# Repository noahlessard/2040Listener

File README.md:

## 2040Listener

This project contains the Raspberry Pi Pico C SDK Project, and Kicad PCB Project, to manufacture an open source MITM style keystroke interceptor. This style of device intercepts a host's computer request to get keystrokes, relays it to a real USB keyboard, and while returning the responses of typed keys, logs it to a LittleFS file stored in flash memory. This memory persists, and can be accessed through a CDC serial port. This port can be toggled on/off for a "stealth" mode.

USB host/device communication is done using the PIO of Raspberry Pi Pico (RP2040). I built the software with the VSCode Pico Project Extension. It uses several other open source libraries, which can be found in the credits section at the bottom of this readme. 

The PCB is designed around the 0805 footprint for easier soldering, and a simple 2 layer board for cheaper manufacturing.

The general idea of the firmware architecture is that core0 of the 2040 acts as a "fake" USB device to the victim computer, sending both HID and CDC data over USB. Core1 acts as a "fake" host stack to a keyboard. Core1 handles getting data from the HID devices, parsing out what the keystroke is and writes to the 2040's LittleFS file before core0 actually transmits. For more details, see my blog post: https://nlessard.online/projects/2040listener/.

**If you decide to build this device yourself, please use it for educational purposes only, and never use it on a computer that you don't control!**

## GPIO 
(This section is useful for testing on a normal Pico board, where access to GP pins is easier.)
|VCC|VBUS|
|-|-|
|D-|GP 1|
|D+|GP 0|
|CNC Toggle|GP 17|
|Ground|GND|

## Credits
Dual host + device listener example from here: https://github.com/brendena/pico_device_and_host, although I used a fork for the Pico VS Code extension: https://github.com/TheLowSpecPC/pico_device_and_host_updated. LittleFS was ported to Pico in this library: https://github.com/tjko/pico-lfs. I used the Raspberry Pi's foundation for a lot of advice during hardware design: https://pip-assets.raspberrypi.com/categories/814-rp2040/documents/RP-008279-DS-1-hardware-design-with-rp2040.pdf

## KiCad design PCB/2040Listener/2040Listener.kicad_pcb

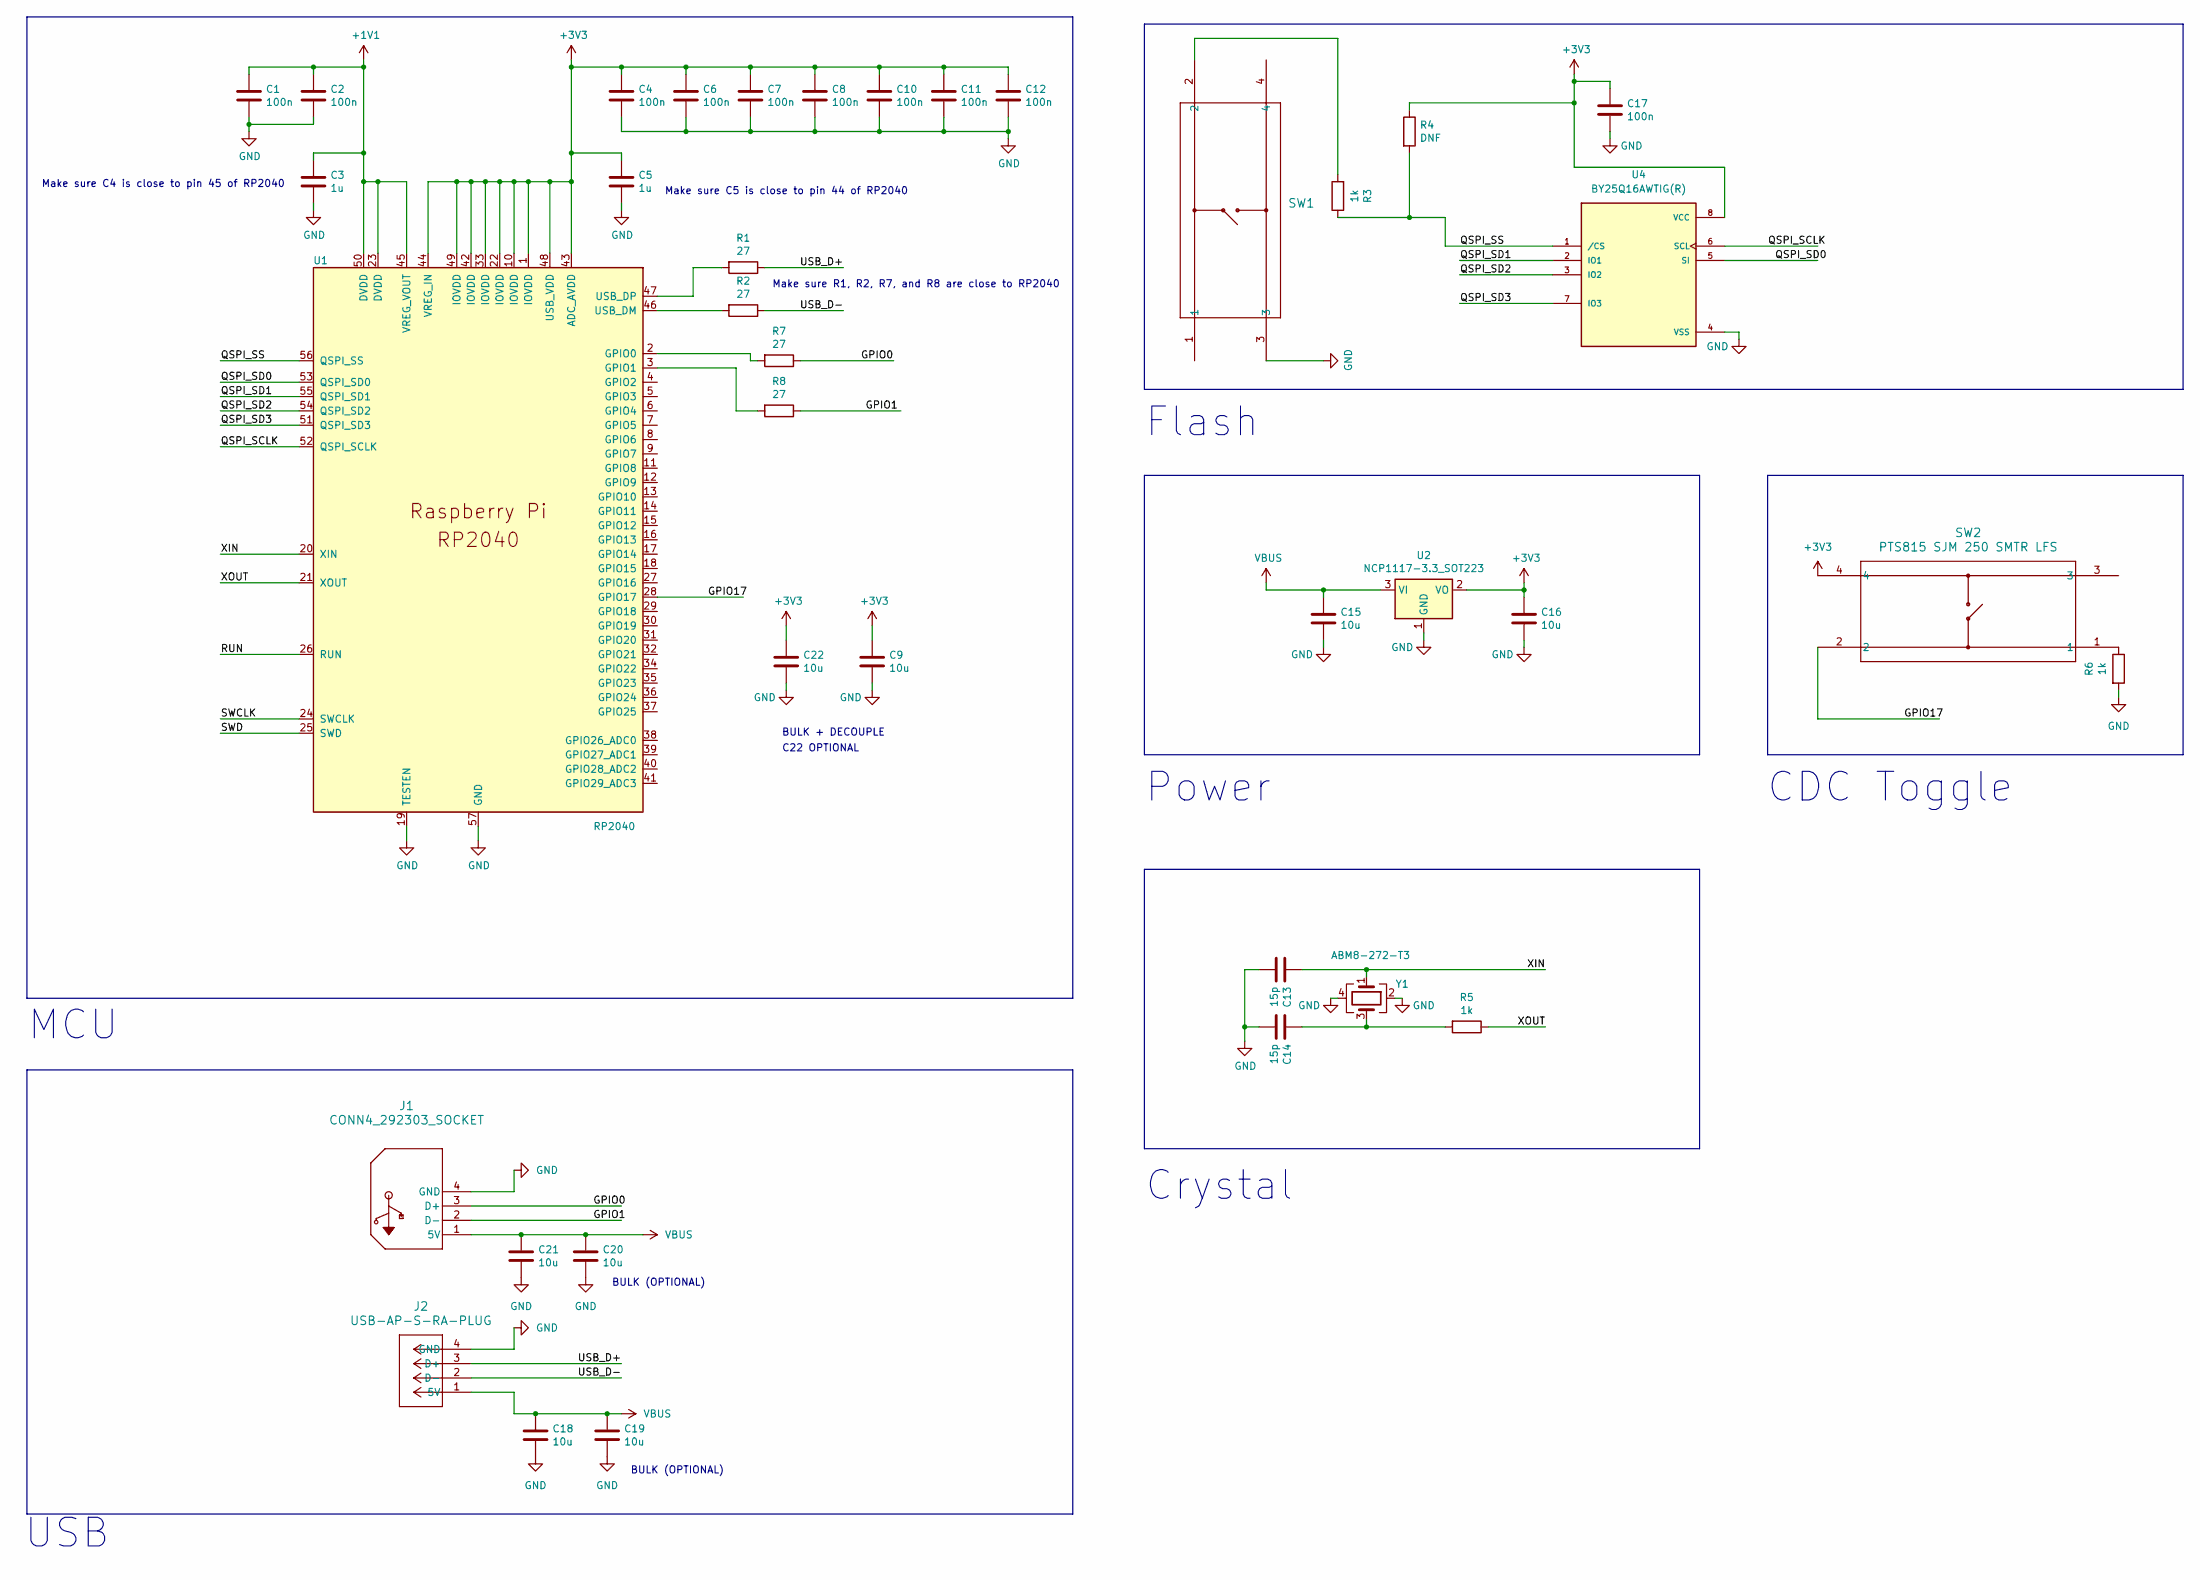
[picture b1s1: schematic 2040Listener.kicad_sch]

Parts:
C1, C2, C4, C6, C7, C8, C10, C11, C12, C17: 100n; C_0805_2012Metric
C3, C5: 1u; C_0805_2012Metric
C9, C15, C16, C18, C19, C20, C21, C22: 10u; C_0805_2012Metric
C13: 15p; D_0805_2012Metric
C14: 15p; C_0805_2012Metric
J1: CONN4_292303_SOCKET; CONN4_292303_TEC
J2: USB-AP-S-RA-PLUG; CONN_USB-AP-S-RA-SMT_ADM
R1, R2, R7, R8: 27; R_0805_2012Metric
R3, R5, R6: 1k; R_0805_2012Metric
R4: DNF; R_0805_2012Metric
SW1, SW2: PTS815 SJM 250 SMTR LFS; SW4_PTS815 SJM 250 SMTR LFS_CNK
U1: RP2040; RP2040-QFN-56
U2: NCP1117-3.3_SOT223; SOT-223-3_TabPin2
U4: BY25Q16AWTIG(R); SOIC127P600X175-8N
Y1: ABM8-272-T3; Crystal_SMD_3225-4Pin_3.2x2.5mm

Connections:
+1V1: C1.1, C2.1, C3.1, U1.23 (DVDD), U1.45 (VREG_VOUT), U1.50 (DVDD)
+3V3: C4.1, C5.1, C6.1, C7.1, C8.1, C9.1, C10.1, C11.1, C12.1, C16.1, C17.1, C22.1, R4.1, SW2.4, U1.1 (IOVDD), U1.10 (IOVDD), U1.22 (IOVDD), U1.33 (IOVDD), U1.42 (IOVDD), U1.43 (ADC_AVDD), U1.44 (VREG_IN), U1.48 (USB_VDD), U1.49 (IOVDD), U2.2 (VO), U4.8 (VCC)
/GPIO0: J1.3 (D+), R7.1
/GPIO1: J1.2 (D-), R8.1
/GPIO17: SW2.2, U1.28 (GPIO17)
/QSPI_SCLK: U1.52 (QSPI_SCLK), U4.6 (SCL)
/QSPI_SD0: U1.53 (QSPI_SD0), U4.5 (SI)
/QSPI_SD1: U1.55 (QSPI_SD1), U4.2 (IO1)
/QSPI_SD2: U1.54 (QSPI_SD2), U4.3 (IO2)
/QSPI_SD3: U1.51 (QSPI_SD3), U4.7 (IO3)
/QSPI_SS: R3.1, R4.2, U1.56 (QSPI_SS), U4.1 (/CS)
/RUN: U1.26 (RUN)
/SWCLK: U1.24 (SWCLK)
/SWD: U1.25 (SWD)
/USB_D+: J2.3 (D+), R1.1
/USB_D-: J2.2 (D-), R2.1
/XIN: C13.1, U1.20 (XIN), Y1.1
/XOUT: R5.1, U1.21 (XOUT)
GND: C1.2, C2.2, C3.2, C4.2, C5.2, C6.2, C7.2, C8.2, C9.2, C10.2, C11.2, C12.2, C13.2, C14.2, C15.2, C16.2, C17.2, C18.2, C19.2, C20.2, C21.2, C22.2, J1.4 (GND), J2.4 (GND), R6.2, SW1.3, U1.19 (TESTEN), U1.57 (GND), U2.1 (GND), U4.4 (VSS), Y1.2, Y1.4
unnamed: C14.1, R5.2, Y1.3
unnamed: R3.2, SW1.2
unnamed: R6.1, SW2.1
unnamed: R7.2, U1.2 (GPIO0)
unnamed: R8.2, U1.3 (GPIO1)
unnamed: R2.2, U1.46 (USB_DM)
unnamed: R1.2, U1.47 (USB_DP)
VBUS: C15.1, C18.1, C19.1, C20.1, C21.1, J1.1 (5V), J2.1 (5V), U2.3 (VI)

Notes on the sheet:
Power
BULK (OPTIONAL)
USB
C22 OPTIONAL
Make sure C5 is close to pin 44 of RP2040
Make sure R1, R2, R7, and R8 are close to RP2040
BULK + DECOUPLE
CDC Toggle
Crystal
Flash
MCU
Make sure C4 is close to pin 45 of RP2040

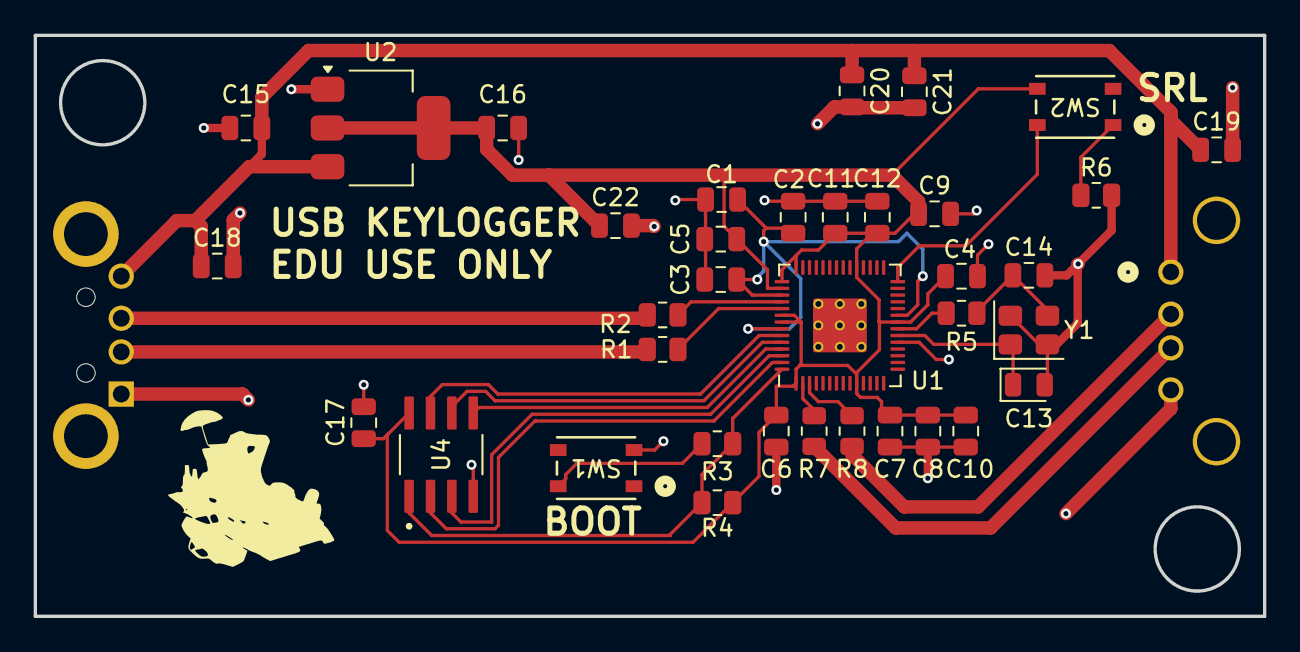
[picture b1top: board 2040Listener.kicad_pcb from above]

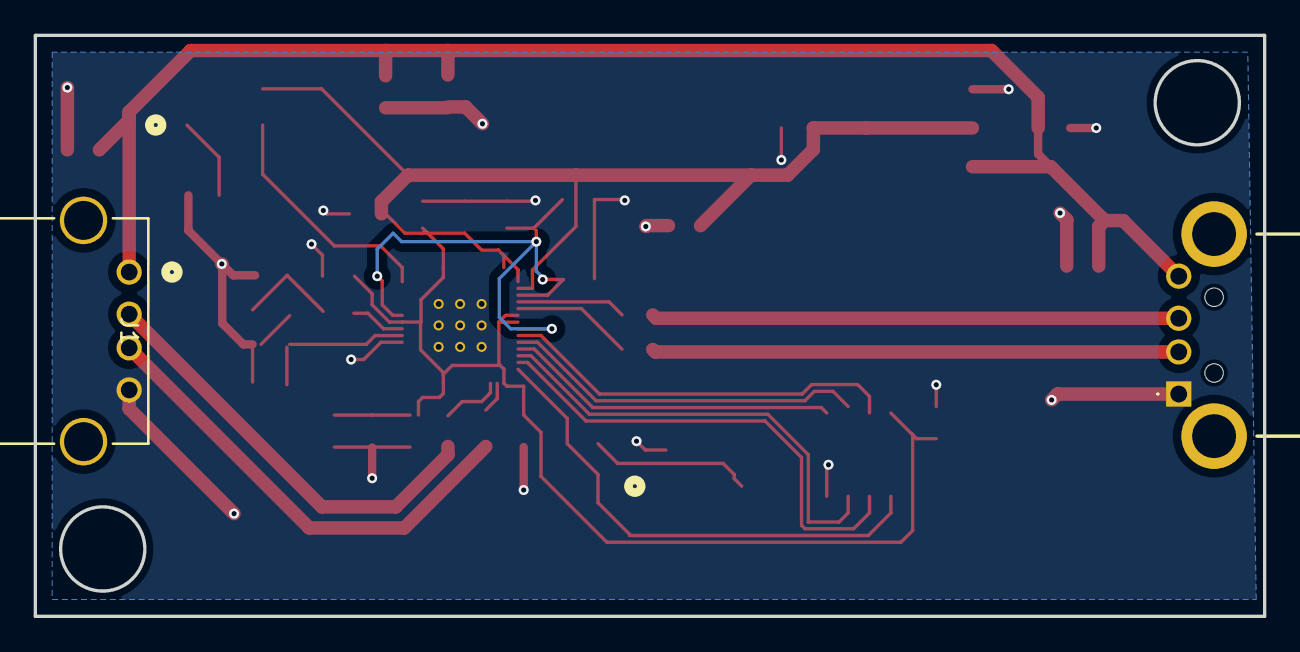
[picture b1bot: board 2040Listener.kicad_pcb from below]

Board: 2 copper layers, 73.0 x 34.5 mm, 38 parts (2 on the bottom side), 24 nets.

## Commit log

2025-12-23 init commit
2025-12-23 including build files
2025-12-23 personal comments for understanding
2025-12-23 fix README
2025-12-23 basic command parsing
2025-12-23 basic stealth mode
2025-12-23 stealth descriptors
2025-12-25 correct toggle func, readme update
2025-12-25 add littlefs
2025-12-25 commit littlefs
2025-12-25 fix LFS for multicore
2025-12-26 working char logging
2025-12-28 add help command
2025-12-29 start kicad
2025-12-29 change to 0805
2025-12-30 update pcb, symbols
2025-12-30 routing
2026-01-01 reposition elements for better routing
2026-01-01 first gerber
2026-01-01 fix small footprint
2026-01-03 update schematic text
2026-02-13 attempt to fix usb connector
2026-03-05 changes right before rotation
2026-03-05 flip usb plugs
2026-03-12 pcb works!
2026-03-13 change gpio
2026-03-15 update pcb spacing
2026-03-16 update pcb image
2026-04-04 Remove junk, add test CI
2026-04-04 Git ignore update
2026-04-23 update html ibom
